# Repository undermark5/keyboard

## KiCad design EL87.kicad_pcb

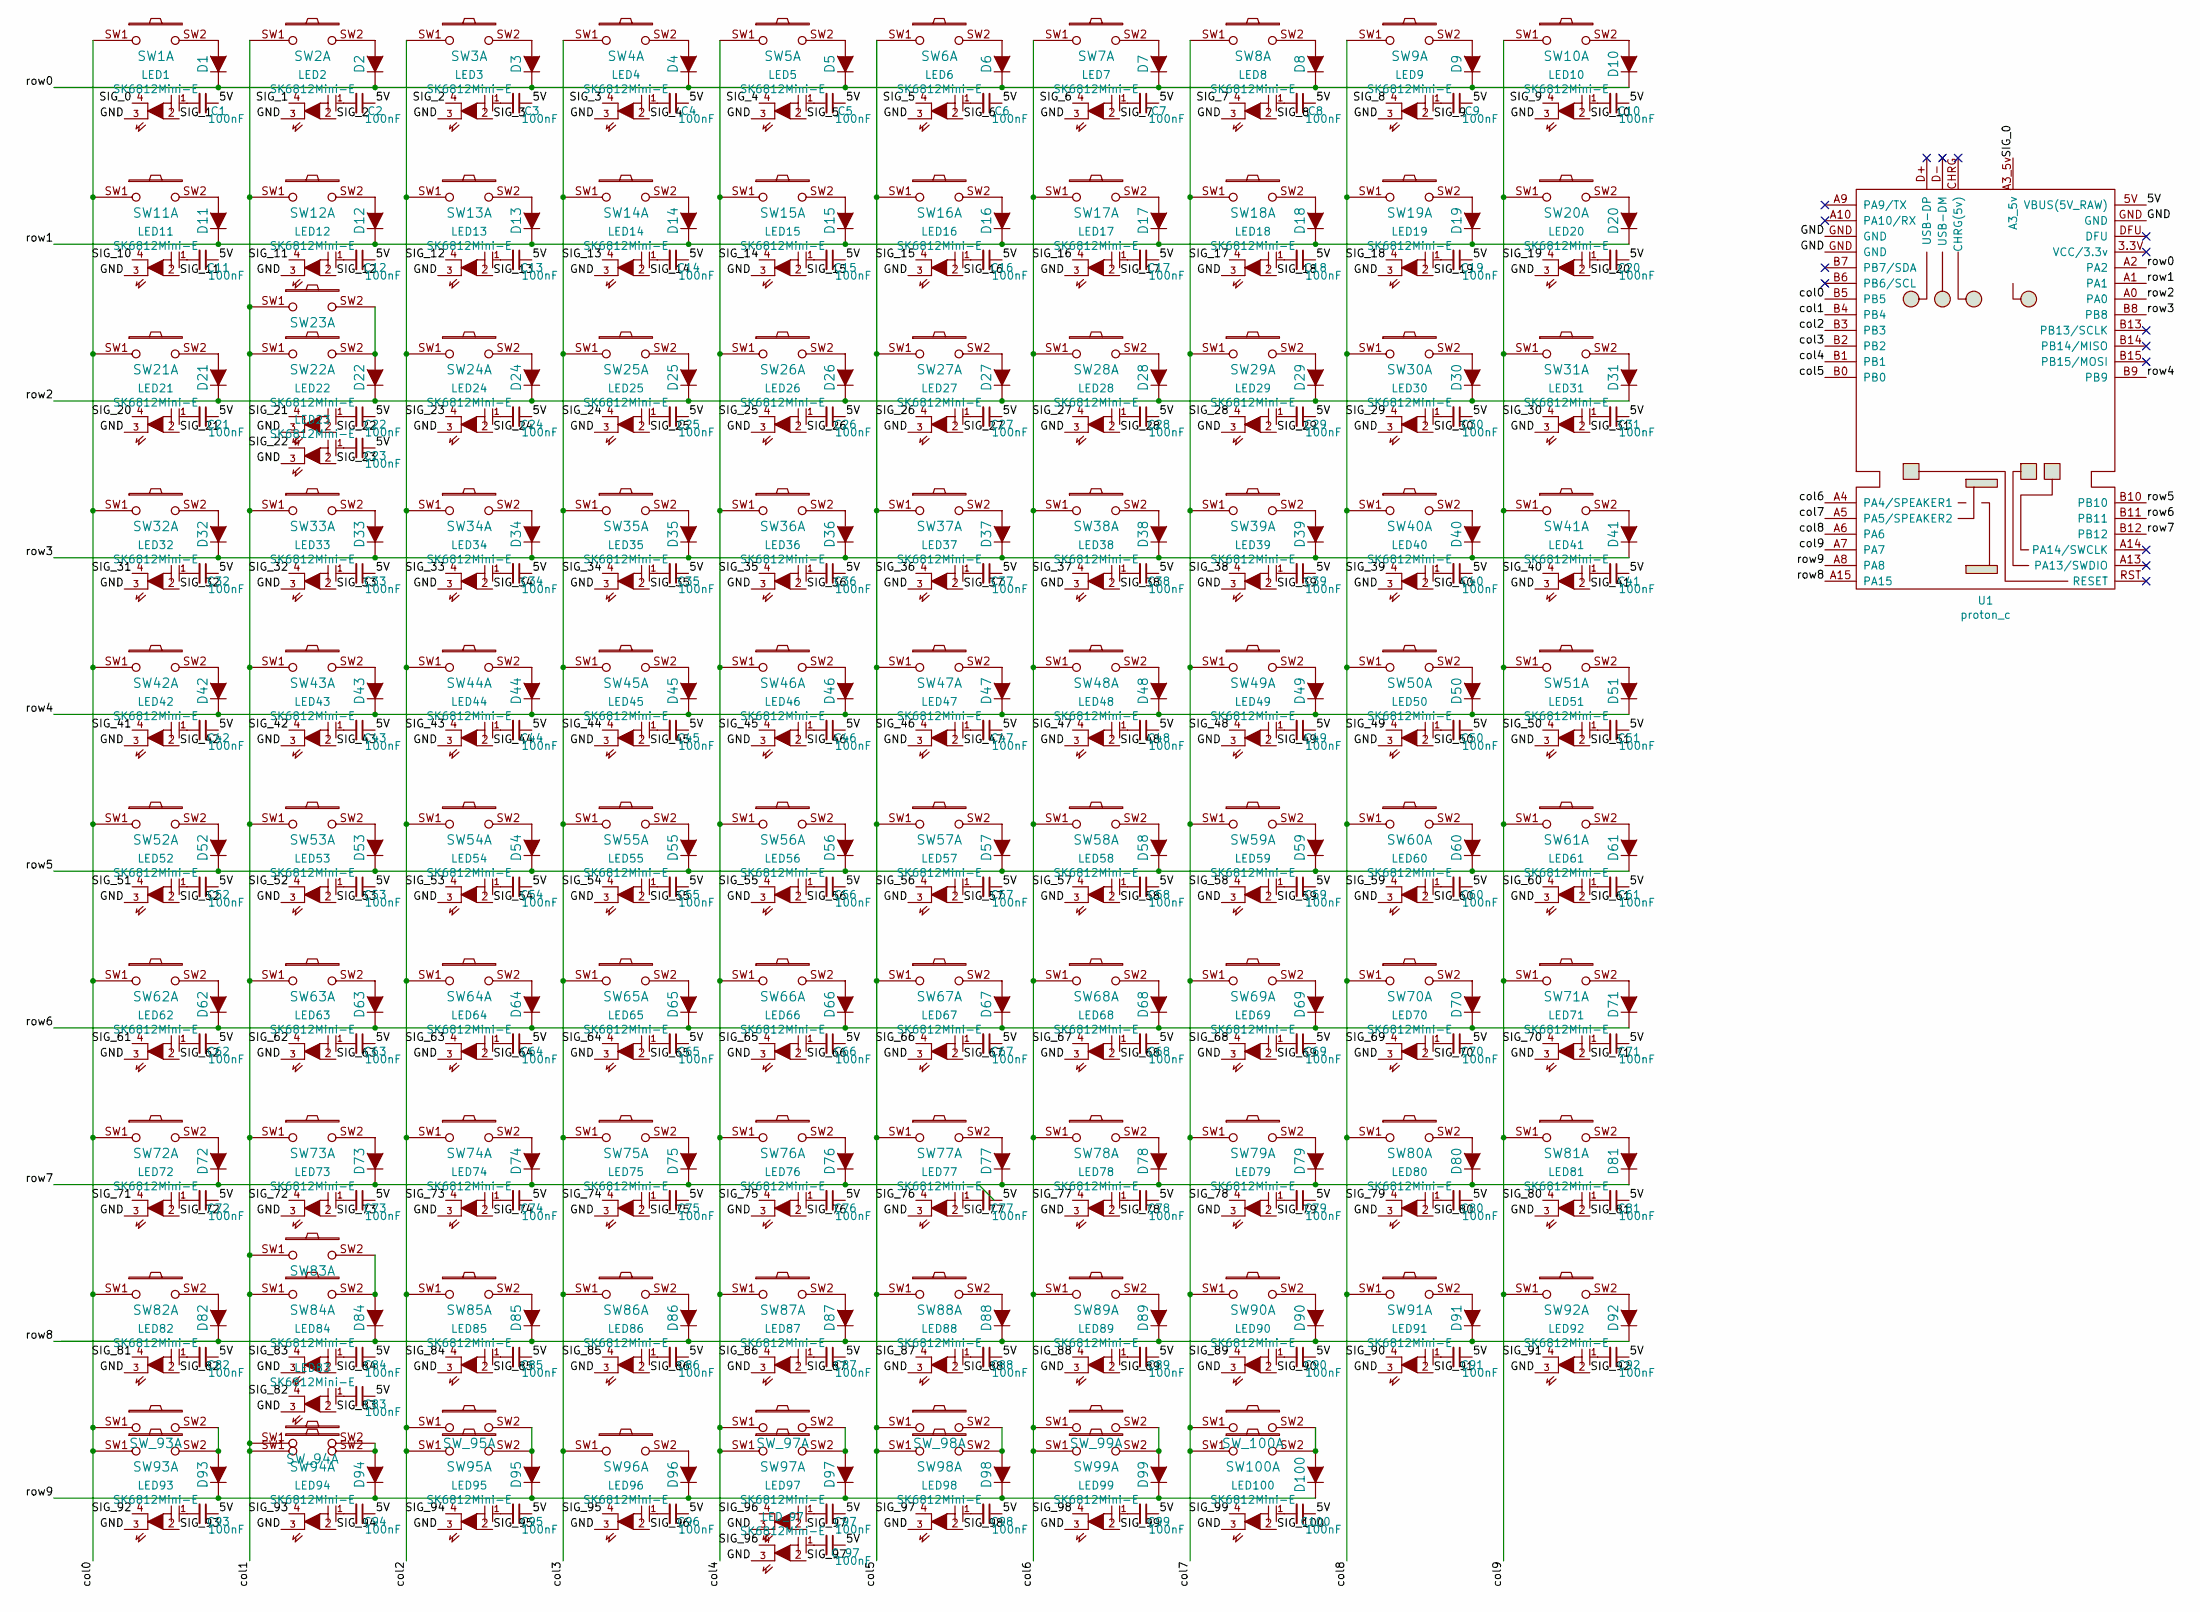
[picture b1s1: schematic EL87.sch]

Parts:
C1, C2, C3, C4, C5, C6, C7, C8, C9, C10, C11, C12, C13, C14, C15, C16, C17, C18, C19, C20, C21, C22, C23, C24, C25, C26, C27, C28, C29, C30, C31, C32, C33, C34, C35, C36, C37, C38, C39, C40, C41, C42, C43, C44, C45, C46, C47, C48, C49, C50, C51, C52, C53, C54, C55, C56, C57, C58, C59, C60, C61, C62, C63, C64, C65, C66, C67, C68, C69, C70, C71, C72, C73, C74, C75, C76, C77, C78, C79, C80, C81, C82, C83, C84, C85, C86, C87, C88, C89, C90, C91, C92, C93, C94, C95, C96, C97, C98, C99, C100: 100nF; MX-1U-0805
C_97: 100nF; MX-1U-0805
D1, D2, D3, D4, D5, D6, D7, D8, D9, D10, D11, D12, D13, D14, D15, D16, D17, D18, D19, D20, D21, D22, D24, D25, D26, D27, D28, D29, D30, D31, D32, D33, D34, D35, D36, D37, D38, D39, D40, D41, D42, D43, D44, D45, D46, D47, D48, D49, D50, D51, D52, D53, D54, D55, D56, D57, D58, D59, D60, D61, D62, D63, D64, D65, D66, D67, D68, D69, D70, D71, D72, D73, D74, D75, D76, D77, D78, D79, D80, D81, D82, D84, D85, D86, D87, D88, D89, D90, D91, D92, D93, D94, D95, D96, D97, D98, D99, D100: D; D_SOD-123_HandSoldering
LED1, LED2, LED3, LED4, LED5, LED6, LED7, LED8, LED9, LED10, LED11, LED12, LED13, LED14, LED15, LED16, LED17, LED18, LED19, LED20, LED21, LED22, LED23, LED24, LED25, LED26, LED27, LED28, LED29, LED30, LED31, LED32, LED33, LED34, LED35, LED36, LED37, LED38, LED39, LED40, LED41, LED42, LED43, LED44, LED45, LED46, LED47, LED48, LED49, LED50, LED51, LED52, LED53, LED54, LED55, LED56, LED57, LED58, LED59, LED60, LED61, LED62, LED63, LED64, LED65, LED66, LED67, LED68, LED69, LED70, LED71, LED72, LED73, LED74, LED75, LED76, LED77, LED78, LED79, LED80, LED81, LED82, LED83, LED84, LED85, LED86, LED87, LED88, LED89, LED90, LED91, LED92, LED93, LED94, LED95, LED96, LED97, LED98, LED99, LED100: SK6812Mini-E; MX-1U-KS6812Mini-E
LED_97: SK6812Mini-E; MX-1U-KS6812Mini-E
SW1: ESC; MXALPS
SW2: F1; MXALPS
SW3: F2; MXALPS
SW4: F3; MXALPS
SW5: F4; MXALPS
SW6: F5; MXALPS
SW7: F6; MXALPS_1.5U
SW8: F7; MXALPS
SW9: F8; MXALPS
SW10: F9; MXALPS
SW11: F10; MXALPS
SW12: F11; MXALPS
SW13: F12; MXALPS
SW14: PrtScrn; MXALPS
SW15: ScrlLck; MXALPS
SW16: PB; MXALPS
SW17: NumLck; MXALPS
SW18, SW26: -; MXALPS
SW19: PgUp; MXALPS
SW20: Home; MXALPS
SW21: Insert; MXALPS
SW22: BckSpc_split; MXALPS
SW23: BckSpc_2; MXALPS_2U
SW24: BckSpc_Split_2; MXALPS
SW25: =; MXALPS
SW27, SW92: 0; MXALPS
SW28: 9; MXALPS
SW29: 8; MXALPS
SW30: 7; MXALPS
SW31, SW56: 6; MXALPS
SW32: 5; MXALPS
SW33, SW58: 4; MXALPS
SW34, SW88: 3; MXALPS
SW35, SW87: 2; MXALPS
SW36, SW86: 1; MXALPS
SW37: GRAVE; MXALPS
SW38: Tab_1.5; MXALPS_1.5U
SW39: Q; MXALPS
SW40: W; MXALPS
SW41: E; MXALPS
SW42: R; MXALPS
SW43: T; MXALPS
SW44: Y; MXALPS
SW45: U; MXALPS
SW46: I; MXALPS
SW47: O; MXALPS
SW48: P; MXALPS
SW49: [; MXALPS
SW50: ]; MXALPS
SW51: \\; MXALPS
SW52: DEL; MXALPS
SW53: END; MXALPS
SW54: PGDN; MXALPS
SW55: +; MXALPS
SW57: 5; MXALPS_1.75U
SW59: Enter_2.25; MXALPS_2.25U
SW60: APOSTROPHE; MXALPS
SW61: ;; MXALPS
SW62: L; MXALPS
SW63: K; MXALPS
SW64: J; MXALPS
SW65: H; MXALPS
SW66: G; MXALPS
SW67: F; MXALPS
SW68: D; MXALPS
SW69: S; MXALPS
SW70: A; MXALPS
SW71: CAPS_1.75; MXALPS_1.75U
SW72: SHIFT_2.25; MXALPS_2.25U
SW73: Z; MXALPS
SW74: X; MXALPS
SW75: C; MXALPS
SW76: V; MXALPS
SW77: B; MXALPS
SW78: N; MXALPS
SW79: M; MXALPS
SW80: ,; MXALPS
SW81, SW90: .; MXALPS
SW82: /; MXALPS
SW83: Shift_split_1.75; MXALPS_1.75U
SW84: Shift_2.75; MXALPS_2.75U
SW85: Shift_split_fn; MXALPS
SW89: Enter; MXALPS
SW91: 00; MXALPS
SW93: Ctrl_1.25; MXALPS_1.25U
SW94: MENU_1.25; MXALPS_1.25U
SW95, SW99: GUI_1.25; MXALPS_1.25U
SW96, SW98: ALT_1.25; MXALPS_1.25U
SW97: SPACE_6.25; MXALPS_6.25U
SW100: CTRL_1.25; MXALPS_1.25U
SW_93, SW_100: CTRL_1.5; MXALPS_1.5U
SW_94, SW_99: GUI; MXALPS
SW_95, SW_98: ALT_1.5; MXALPS_1.5U
SW_97: SPACE_7; MXALPS_7U
U1: proton_c

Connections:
/5V: C1.1, C2.1, C3.1, C4.1, C5.1, C6.1, C7.1, C8.1, C9.1, C10.1, C11.1, C12.1, C13.1, C14.1, C15.1, C16.1, C17.1, C18.1, C19.1, C20.1, C21.1, C22.1, C23.1, C24.1, C25.1, C26.1, C27.1, C28.1, C29.1, C30.1, C31.1, C32.1, C33.1, C34.1, C35.1, C36.1, C37.1, C38.1, C39.1, C40.1, C41.1, C42.1, C43.1, C44.1, C45.1, C46.1, C47.1, C48.1, C49.1, C50.1, C51.1, C52.1, C53.1, C54.1, C55.1, C56.1, C57.1, C58.1, C59.1, C60.1, C61.1, C62.1, C63.1, C64.1, C65.1, C66.1, C67.1, C68.1, C69.1, C70.1, C71.1, C72.1, C73.1, C74.1, C75.1, C76.1, C77.1, C78.1, C79.1, C80.1, C81.1, C82.1, C83.1, C84.1, C85.1, C86.1, C87.1, C88.1, C89.1, C90.1, C91.1, C92.1, C93.1, C94.1, C95.1, C96.1, C97.1, C98.1, C99.1, C100.1, C_97.1, U1.5V (VBUS(5V_RAW))
/GND: LED1.3 (GND), LED2.3 (GND), LED3.3 (GND), LED4.3 (GND), LED5.3 (GND), LED6.3 (GND), LED7.3 (GND), LED8.3 (GND), LED9.3 (GND), LED10.3 (GND), LED11.3 (GND), LED12.3 (GND), LED13.3 (GND), LED14.3 (GND), LED15.3 (GND), LED16.3 (GND), LED17.3 (GND), LED18.3 (GND), LED19.3 (GND), LED20.3 (GND), LED21.3 (GND), LED22.3 (GND), LED23.3 (GND), LED24.3 (GND), LED25.3 (GND), LED26.3 (GND), LED27.3 (GND), LED28.3 (GND), LED29.3 (GND), LED30.3 (GND), LED31.3 (GND), LED32.3 (GND), LED33.3 (GND), LED34.3 (GND), LED35.3 (GND), LED36.3 (GND), LED37.3 (GND), LED38.3 (GND), LED39.3 (GND), LED40.3 (GND), LED41.3 (GND), LED42.3 (GND), LED43.3 (GND), LED44.3 (GND), LED45.3 (GND), LED46.3 (GND), LED47.3 (GND), LED48.3 (GND), LED49.3 (GND), LED50.3 (GND), LED51.3 (GND), LED52.3 (GND), LED53.3 (GND), LED54.3 (GND), LED55.3 (GND), LED56.3 (GND), LED57.3 (GND), LED58.3 (GND), LED59.3 (GND), LED60.3 (GND), LED61.3 (GND), LED62.3 (GND), LED63.3 (GND), LED64.3 (GND), LED65.3 (GND), LED66.3 (GND), LED67.3 (GND), LED68.3 (GND), LED69.3 (GND), LED70.3 (GND), LED71.3 (GND), LED72.3 (GND), LED73.3 (GND), LED74.3 (GND), LED75.3 (GND), LED76.3 (GND), LED77.3 (GND), LED78.3 (GND), LED79.3 (GND), LED80.3 (GND), LED81.3 (GND), LED82.3 (GND), LED83.3 (GND), LED84.3 (GND), LED85.3 (GND), LED86.3 (GND), LED87.3 (GND), LED88.3 (GND), LED89.3 (GND), LED90.3 (GND), LED91.3 (GND), LED92.3 (GND), LED93.3 (GND), LED94.3 (GND), LED95.3 (GND), LED96.3 (GND), LED97.3 (GND), LED98.3 (GND), LED99.3 (GND), LED100.3 (GND), LED_97.3 (GND), U1.GND
/SIG_0: LED1.4 (D_IN), U1.A3_5v
/SIG_1: LED1.2 (D_OUT), LED2.4 (D_IN)
/SIG_2: LED2.2 (D_OUT), LED3.4 (D_IN)
/SIG_3: LED3.2 (D_OUT), LED4.4 (D_IN)
/SIG_4: LED4.2 (D_OUT), LED5.4 (D_IN)
/SIG_5: LED5.2 (D_OUT), LED6.4 (D_IN)
/SIG_6: LED6.2 (D_OUT), LED7.4 (D_IN)
/SIG_7: LED7.2 (D_OUT), LED8.4 (D_IN)
/SIG_8: LED8.2 (D_OUT), LED9.4 (D_IN)
/SIG_9: LED9.2 (D_OUT), LED10.4 (D_IN)
/SIG_10: LED10.2 (D_OUT), LED11.4 (D_IN)
/SIG_11: LED11.2 (D_OUT), LED12.4 (D_IN)
/SIG_12: LED12.2 (D_OUT), LED13.4 (D_IN)
/SIG_13: LED13.2 (D_OUT), LED14.4 (D_IN)
/SIG_14: LED14.2 (D_OUT), LED15.4 (D_IN)
/SIG_15: LED15.2 (D_OUT), LED16.4 (D_IN)
/SIG_16: LED16.2 (D_OUT), LED17.4 (D_IN)
/SIG_17: LED17.2 (D_OUT), LED18.4 (D_IN)
/SIG_18: LED18.2 (D_OUT), LED19.4 (D_IN)
/SIG_19: LED19.2 (D_OUT), LED20.4 (D_IN)
/SIG_20: LED20.2 (D_OUT), LED21.4 (D_IN)
/SIG_21: LED21.2 (D_OUT), LED22.4 (D_IN); also elsewhere on the board
/SIG_22: LED22.2 (D_OUT), LED23.4 (D_IN); also elsewhere on the board
/SIG_23: LED23.2 (D_OUT), LED24.4 (D_IN); also elsewhere on the board
/SIG_24: LED24.2 (D_OUT), LED25.4 (D_IN); also elsewhere on the board
/SIG_25: LED25.2 (D_OUT), LED26.4 (D_IN)
/SIG_26: LED26.2 (D_OUT), LED27.4 (D_IN)
/SIG_27: LED27.2 (D_OUT), LED28.4 (D_IN)
/SIG_28: LED28.2 (D_OUT), LED29.4 (D_IN)
/SIG_29: LED29.2 (D_OUT), LED30.4 (D_IN)
/SIG_30: LED30.2 (D_OUT), LED31.4 (D_IN)
/SIG_31: LED31.2 (D_OUT), LED32.4 (D_IN)
/SIG_32: LED32.2 (D_OUT), LED33.4 (D_IN)
/SIG_33: LED33.2 (D_OUT), LED34.4 (D_IN)
/SIG_34: LED34.2 (D_OUT), LED35.4 (D_IN)
/SIG_35: LED35.2 (D_OUT), LED36.4 (D_IN)
/SIG_36: LED36.2 (D_OUT), LED37.4 (D_IN)
/SIG_37: LED37.2 (D_OUT), LED38.4 (D_IN)
/SIG_38: LED38.2 (D_OUT), LED39.4 (D_IN)
/SIG_39: LED39.2 (D_OUT), LED40.4 (D_IN)
/SIG_40: LED40.2 (D_OUT), LED41.4 (D_IN)
/SIG_41: LED41.2 (D_OUT), LED42.4 (D_IN)
/SIG_42: LED42.2 (D_OUT), LED43.4 (D_IN)
/SIG_43: LED43.2 (D_OUT), LED44.4 (D_IN)
/SIG_44: LED44.2 (D_OUT), LED45.4 (D_IN)
/SIG_45: LED45.2 (D_OUT), LED46.4 (D_IN)
/SIG_46: LED46.2 (D_OUT), LED47.4 (D_IN)
/SIG_47: LED47.2 (D_OUT), LED48.4 (D_IN)
/SIG_48: LED48.2 (D_OUT), LED49.4 (D_IN)
/SIG_49: LED49.2 (D_OUT), LED50.4 (D_IN)
/SIG_50: LED50.2 (D_OUT), LED51.4 (D_IN)
/SIG_51: LED51.2 (D_OUT), LED52.4 (D_IN)
/SIG_52: LED52.2 (D_OUT), LED53.4 (D_IN)
/SIG_53: LED53.2 (D_OUT), LED54.4 (D_IN)
/SIG_54: LED54.2 (D_OUT), LED55.4 (D_IN)
/SIG_55: LED55.2 (D_OUT), LED56.4 (D_IN)
/SIG_56: LED56.2 (D_OUT), LED57.4 (D_IN)
/SIG_57: LED57.2 (D_OUT), LED58.4 (D_IN)
/SIG_58: LED58.2 (D_OUT), LED59.4 (D_IN)
/SIG_59: LED59.2 (D_OUT), LED60.4 (D_IN)
/SIG_60: LED60.2 (D_OUT), LED61.4 (D_IN)
/SIG_61: LED61.2 (D_OUT), LED62.4 (D_IN)
/SIG_62: LED62.2 (D_OUT), LED63.4 (D_IN)
/SIG_63: LED63.2 (D_OUT), LED64.4 (D_IN)
/SIG_64: LED64.2 (D_OUT), LED65.4 (D_IN)
/SIG_65: LED65.2 (D_OUT), LED66.4 (D_IN)
/SIG_66: LED66.2 (D_OUT), LED67.4 (D_IN)
/SIG_67: LED67.2 (D_OUT), LED68.4 (D_IN)
/SIG_68: LED68.2 (D_OUT), LED69.4 (D_IN)
/SIG_69: LED69.2 (D_OUT), LED70.4 (D_IN)
/SIG_70: LED70.2 (D_OUT), LED71.4 (D_IN)
/SIG_71: LED71.2 (D_OUT), LED72.4 (D_IN)
/SIG_72: LED72.2 (D_OUT), LED73.4 (D_IN)
/SIG_73: LED73.2 (D_OUT), LED74.4 (D_IN)
/SIG_74: LED74.2 (D_OUT), LED75.4 (D_IN)
/SIG_75: LED75.2 (D_OUT), LED76.4 (D_IN)
/SIG_76: LED76.2 (D_OUT), LED77.4 (D_IN)
/SIG_77: LED77.2 (D_OUT), LED78.4 (D_IN)
/SIG_78: LED78.2 (D_OUT), LED79.4 (D_IN)
/SIG_79: LED79.2 (D_OUT), LED80.4 (D_IN)
/SIG_80: LED80.2 (D_OUT), LED81.4 (D_IN)
/SIG_81: LED81.2 (D_OUT), LED82.4 (D_IN)
/SIG_82: LED82.2 (D_OUT), LED83.4 (D_IN); also elsewhere on the board
/SIG_83: LED83.2 (D_OUT), LED84.4 (D_IN); also elsewhere on the board
/SIG_84: LED84.2 (D_OUT), LED85.4 (D_IN); also elsewhere on the board
/SIG_85: LED85.2 (D_OUT), LED86.4 (D_IN); also elsewhere on the board
/SIG_86: LED86.2 (D_OUT), LED87.4 (D_IN)
/SIG_87: LED87.2 (D_OUT), LED88.4 (D_IN)
/SIG_88: LED88.2 (D_OUT), LED89.4 (D_IN)
/SIG_89: LED89.2 (D_OUT), LED90.4 (D_IN)
/SIG_90: LED90.2 (D_OUT), LED91.4 (D_IN)
/SIG_91: LED91.2 (D_OUT), LED92.4 (D_IN)
/SIG_92: LED92.2 (D_OUT), LED93.4 (D_IN)
/SIG_93: LED93.2 (D_OUT), LED94.4 (D_IN)
/SIG_94: LED94.2 (D_OUT), LED95.4 (D_IN)
/SIG_95: LED95.2 (D_OUT), LED96.4 (D_IN); also elsewhere on the board
/SIG_96: LED96.2 (D_OUT), LED97.4 (D_IN), LED_97.4 (D_IN); also elsewhere on the board
/SIG_97: LED97.2 (D_OUT), LED98.4 (D_IN), LED_97.2 (D_OUT)
/SIG_98: LED98.2 (D_OUT), LED99.4 (D_IN)
/SIG_99: LED99.2 (D_OUT), LED100.4 (D_IN)
/SIG_100: LED100.2 (D_OUT)
/col0: SW1.SW1, SW11.SW1, SW21.SW1, SW32.SW1, SW42.SW1, SW52.SW1, SW62.SW1, SW72.SW1, SW82.SW1, SW93.SW1, SW_93.SW1, U1.B5
/col1: SW2.SW1, SW12.SW1, SW22.SW1, SW23.SW1, SW33.SW1, SW43.SW1, SW53.SW1, SW63.SW1, SW73.SW1, SW83.SW1, SW84.SW1, SW94.SW1, SW_94.SW1, U1.B4
/col2: SW3.SW1, SW13.SW1, SW24.SW1, SW34.SW1, SW44.SW1, SW54.SW1, SW64.SW1, SW74.SW1, SW85.SW1, SW95.SW1, SW_95.SW1, U1.B3
/col3: SW4.SW1, SW14.SW1, SW25.SW1, SW35.SW1, SW45.SW1, SW55.SW1, SW65.SW1, SW75.SW1, SW86.SW1, SW96.SW1, U1.B2
/col4: SW5.SW1, SW15.SW1, SW26.SW1, SW36.SW1, SW46.SW1, SW56.SW1, SW66.SW1, SW76.SW1, SW87.SW1, SW97.SW1, SW_97.SW1, U1.B1
/col5: SW6.SW1, SW16.SW1, SW27.SW1, SW37.SW1, SW47.SW1, SW57.SW1, SW67.SW1, SW77.SW1, SW88.SW1, SW98.SW1, SW_98.SW1, U1.B0
/col6: SW7.SW1, SW17.SW1, SW28.SW1, SW38.SW1, SW48.SW1, SW58.SW1, SW68.SW1, SW78.SW1, SW89.SW1, SW99.SW1, SW_99.SW1, U1.A4 (PA4/SPEAKER1)
/col7: SW8.SW1, SW18.SW1, SW29.SW1, SW39.SW1, SW49.SW1, SW59.SW1, SW69.SW1, SW79.SW1, SW90.SW1, SW100.SW1, SW_100.SW1, U1.A5 (PA5/SPEAKER2)
/col8: SW9.SW1, SW19.SW1, SW30.SW1, SW40.SW1, SW50.SW1, SW60.SW1, SW70.SW1, SW80.SW1, SW91.SW1, U1.A6
/col9: SW10.SW1, SW20.SW1, SW31.SW1, SW41.SW1, SW51.SW1, SW61.SW1, SW71.SW1, SW81.SW1, SW92.SW1, U1.A7
/row0: D1.1 (K), D2.1 (K), D3.1 (K), D4.1 (K), D5.1 (K), D6.1 (K), D7.1 (K), D8.1 (K), D9.1 (K), D10.1 (K), U1.A2
/row1: D11.1 (K), D12.1 (K), D13.1 (K), D14.1 (K), D15.1 (K), D16.1 (K), D17.1 (K), D18.1 (K), D19.1 (K), D20.1 (K), U1.A1
/row2: D21.1 (K), D22.1 (K), D24.1 (K), D25.1 (K), D26.1 (K), D27.1 (K), D28.1 (K), D29.1 (K), D30.1 (K), D31.1 (K), U1.A0
/row3: D32.1 (K), D33.1 (K), D34.1 (K), D35.1 (K), D36.1 (K), D37.1 (K), D38.1 (K), D39.1 (K), D40.1 (K), D41.1 (K), U1.B8
/row4: D42.1 (K), D43.1 (K), D44.1 (K), D45.1 (K), D46.1 (K), D47.1 (K), D48.1 (K), D49.1 (K), D50.1 (K), D51.1 (K), U1.B9
/row5: D52.1 (K), D53.1 (K), D54.1 (K), D55.1 (K), D56.1 (K), D57.1 (K), D58.1 (K), D59.1 (K), D60.1 (K), D61.1 (K), U1.B10
/row6: D62.1 (K), D63.1 (K), D64.1 (K), D65.1 (K), D66.1 (K), D67.1 (K), D68.1 (K), D69.1 (K), D70.1 (K), D71.1 (K), U1.B11
/row7: D72.1 (K), D73.1 (K), D74.1 (K), D75.1 (K), D76.1 (K), D77.1 (K), D78.1 (K), D79.1 (K), D80.1 (K), D81.1 (K), U1.B12
/row8: D82.1 (K), D84.1 (K), D85.1 (K), D86.1 (K), D87.1 (K), D88.1 (K), D89.1 (K), D90.1 (K), D91.1 (K), D92.1 (K), U1.A15
/row9: D93.1 (K), D94.1 (K), D95.1 (K), D96.1 (K), D97.1 (K), D98.1 (K), D99.1 (K), D100.1 (K), U1.A8
unnamed: C1.2, LED1.1 (VDD)
unnamed: C2.2, LED2.1 (VDD)
unnamed: C3.2, LED3.1 (VDD)
unnamed: C4.2, LED4.1 (VDD)
unnamed: C5.2, LED5.1 (VDD)
unnamed: C6.2, LED6.1 (VDD)
unnamed: C7.2, LED7.1 (VDD)
unnamed: C8.2, LED8.1 (VDD)
unnamed: C9.2, LED9.1 (VDD)
unnamed: C10.2, LED10.1 (VDD)
unnamed: C11.2, LED11.1 (VDD)
unnamed: C12.2, LED12.1 (VDD)
unnamed: C13.2, LED13.1 (VDD)
unnamed: C14.2, LED14.1 (VDD)
unnamed: C15.2, LED15.1 (VDD)
unnamed: C16.2, LED16.1 (VDD)
unnamed: C17.2, LED17.1 (VDD)
unnamed: C18.2, LED18.1 (VDD)
unnamed: C19.2, LED19.1 (VDD)
unnamed: C20.2, LED20.1 (VDD)
unnamed: C21.2, LED21.1 (VDD)
unnamed: C22.2, LED22.1 (VDD)
unnamed: C23.2, LED23.1 (VDD)
unnamed: C24.2, LED24.1 (VDD)
unnamed: C25.2, LED25.1 (VDD)
unnamed: C26.2, LED26.1 (VDD)
unnamed: C27.2, LED27.1 (VDD)
unnamed: C28.2, LED28.1 (VDD)
unnamed: C29.2, LED29.1 (VDD)
unnamed: C30.2, LED30.1 (VDD)
unnamed: C31.2, LED31.1 (VDD)
unnamed: C32.2, LED32.1 (VDD)
unnamed: C33.2, LED33.1 (VDD)
unnamed: C34.2, LED34.1 (VDD)
unnamed: C35.2, LED35.1 (VDD)
unnamed: C36.2, LED36.1 (VDD)
unnamed: C37.2, LED37.1 (VDD)
unnamed: C38.2, LED38.1 (VDD)
unnamed: C39.2, LED39.1 (VDD)
unnamed: C40.2, LED40.1 (VDD)
unnamed: C41.2, LED41.1 (VDD)
unnamed: C42.2, LED42.1 (VDD)
unnamed: C43.2, LED43.1 (VDD)
unnamed: C44.2, LED44.1 (VDD)
unnamed: C45.2, LED45.1 (VDD)
unnamed: C46.2, LED46.1 (VDD)
unnamed: C47.2, LED47.1 (VDD)
unnamed: C48.2, LED48.1 (VDD)
unnamed: C49.2, LED49.1 (VDD)
unnamed: C50.2, LED50.1 (VDD)
unnamed: C51.2, LED51.1 (VDD)
unnamed: C52.2, LED52.1 (VDD)
unnamed: C53.2, LED53.1 (VDD)
unnamed: C54.2, LED54.1 (VDD)
unnamed: C55.2, LED55.1 (VDD)
unnamed: C56.2, LED56.1 (VDD)
unnamed: C57.2, LED57.1 (VDD)
unnamed: C58.2, LED58.1 (VDD)
unnamed: C59.2, LED59.1 (VDD)
unnamed: C60.2, LED60.1 (VDD)
unnamed: C61.2, LED61.1 (VDD)
unnamed: C62.2, LED62.1 (VDD)
unnamed: C63.2, LED63.1 (VDD)
unnamed: C64.2, LED64.1 (VDD)
unnamed: C65.2, LED65.1 (VDD)
unnamed: C66.2, LED66.1 (VDD)
unnamed: C67.2, LED67.1 (VDD)
unnamed: C68.2, LED68.1 (VDD)
unnamed: C69.2, LED69.1 (VDD)
unnamed: C70.2, LED70.1 (VDD)
unnamed: C71.2, LED71.1 (VDD)
unnamed: C72.2, LED72.1 (VDD)
unnamed: C73.2, LED73.1 (VDD)
unnamed: C74.2, LED74.1 (VDD)
unnamed: C75.2, LED75.1 (VDD)
unnamed: C76.2, LED76.1 (VDD)
unnamed: C77.2, LED77.1 (VDD)
unnamed: C78.2, LED78.1 (VDD)
unnamed: C79.2, LED79.1 (VDD)
unnamed: C80.2, LED80.1 (VDD)
unnamed: C81.2, LED81.1 (VDD)
unnamed: C82.2, LED82.1 (VDD)
unnamed: C83.2, LED83.1 (VDD)
unnamed: C84.2, LED84.1 (VDD)
unnamed: C85.2, LED85.1 (VDD)
unnamed: C86.2, LED86.1 (VDD)
unnamed: C87.2, LED87.1 (VDD)
unnamed: C88.2, LED88.1 (VDD)
unnamed: C89.2, LED89.1 (VDD)
unnamed: C90.2, LED90.1 (VDD)
unnamed: C91.2, LED91.1 (VDD)
unnamed: C92.2, LED92.1 (VDD)
unnamed: C93.2, LED93.1 (VDD)
unnamed: C94.2, LED94.1 (VDD)
unnamed: C95.2, LED95.1 (VDD)
unnamed: C96.2, LED96.1 (VDD)
unnamed: C97.2, LED97.1 (VDD)
unnamed: C98.2, LED98.1 (VDD)
unnamed: C99.2, LED99.1 (VDD)
unnamed: C100.2, LED100.1 (VDD)
unnamed: C_97.2, LED_97.1 (VDD)
unnamed: D1.2 (A), SW1.SW2
unnamed: D2.2 (A), SW2.SW2
unnamed: D3.2 (A), SW3.SW2
unnamed: D4.2 (A), SW4.SW2
unnamed: D5.2 (A), SW5.SW2
unnamed: D6.2 (A), SW6.SW2
unnamed: D7.2 (A), SW7.SW2
unnamed: D8.2 (A), SW8.SW2
unnamed: D9.2 (A), SW9.SW2
unnamed: D10.2 (A), SW10.SW2
unnamed: D11.2 (A), SW11.SW2
unnamed: D12.2 (A), SW12.SW2
unnamed: D13.2 (A), SW13.SW2
unnamed: D14.2 (A), SW14.SW2
unnamed: D15.2 (A), SW15.SW2
unnamed: D16.2 (A), SW16.SW2
unnamed: D17.2 (A), SW17.SW2
unnamed: D18.2 (A), SW18.SW2
unnamed: D19.2 (A), SW19.SW2
unnamed: D20.2 (A), SW20.SW2
unnamed: D21.2 (A), SW21.SW2
unnamed: D22.2 (A), SW22.SW2, SW23.SW2
unnamed: D24.2 (A), SW24.SW2
unnamed: D25.2 (A), SW25.SW2
unnamed: D26.2 (A), SW26.SW2
unnamed: D27.2 (A), SW27.SW2
unnamed: D28.2 (A), SW28.SW2
unnamed: D29.2 (A), SW29.SW2
unnamed: D30.2 (A), SW30.SW2
unnamed: D31.2 (A), SW31.SW2
unnamed: D32.2 (A), SW32.SW2
unnamed: D33.2 (A), SW33.SW2
unnamed: D34.2 (A), SW34.SW2
unnamed: D35.2 (A), SW35.SW2
unnamed: D36.2 (A), SW36.SW2
unnamed: D37.2 (A), SW37.SW2
unnamed: D38.2 (A), SW38.SW2
unnamed: D39.2 (A), SW39.SW2
unnamed: D40.2 (A), SW40.SW2
unnamed: D41.2 (A), SW41.SW2
unnamed: D42.2 (A), SW42.SW2
unnamed: D43.2 (A), SW43.SW2
unnamed: D44.2 (A), SW44.SW2
unnamed: D45.2 (A), SW45.SW2
unnamed: D46.2 (A), SW46.SW2
unnamed: D47.2 (A), SW47.SW2
unnamed: D48.2 (A), SW48.SW2
unnamed: D49.2 (A), SW49.SW2
unnamed: D50.2 (A), SW50.SW2
unnamed: D51.2 (A), SW51.SW2
unnamed: D52.2 (A), SW52.SW2
unnamed: D53.2 (A), SW53.SW2
unnamed: D54.2 (A), SW54.SW2
unnamed: D55.2 (A), SW55.SW2
unnamed: D56.2 (A), SW56.SW2
unnamed: D57.2 (A), SW57.SW2
unnamed: D58.2 (A), SW58.SW2
unnamed: D59.2 (A), SW59.SW2
unnamed: D60.2 (A), SW60.SW2
unnamed: D61.2 (A), SW61.SW2
unnamed: D62.2 (A), SW62.SW2
unnamed: D63.2 (A), SW63.SW2
unnamed: D64.2 (A), SW64.SW2
unnamed: D65.2 (A), SW65.SW2
unnamed: D66.2 (A), SW66.SW2
unnamed: D67.2 (A), SW67.SW2
unnamed: D68.2 (A), SW68.SW2
unnamed: D69.2 (A), SW69.SW2
unnamed: D70.2 (A), SW70.SW2
unnamed: D71.2 (A), SW71.SW2
unnamed: D72.2 (A), SW72.SW2
unnamed: D73.2 (A), SW73.SW2
unnamed: D74.2 (A), SW74.SW2
unnamed: D75.2 (A), SW75.SW2
unnamed: D76.2 (A), SW76.SW2
unnamed: D77.2 (A), SW77.SW2
unnamed: D78.2 (A), SW78.SW2
unnamed: D79.2 (A), SW79.SW2
unnamed: D80.2 (A), SW80.SW2
unnamed: D81.2 (A), SW81.SW2
unnamed: D82.2 (A), SW82.SW2
unnamed: D84.2 (A), SW83.SW2, SW84.SW2
unnamed: D85.2 (A), SW85.SW2
unnamed: D86.2 (A), SW86.SW2
unnamed: D87.2 (A), SW87.SW2
unnamed: D88.2 (A), SW88.SW2
unnamed: D89.2 (A), SW89.SW2
unnamed: D90.2 (A), SW90.SW2
unnamed: D91.2 (A), SW91.SW2
unnamed: D92.2 (A), SW92.SW2
unnamed: D93.2 (A), SW93.SW2, SW_93.SW2
unnamed: D94.2 (A), SW94.SW2, SW_94.SW2
unnamed: D95.2 (A), SW95.SW2, SW_95.SW2
unnamed: D96.2 (A), SW96.SW2
unnamed: D97.2 (A), SW97.SW2, SW_97.SW2
unnamed: D98.2 (A), SW98.SW2, SW_98.SW2
unnamed: D99.2 (A), SW99.SW2, SW_99.SW2
unnamed: D100.2 (A), SW100.SW2, SW_100.SW2

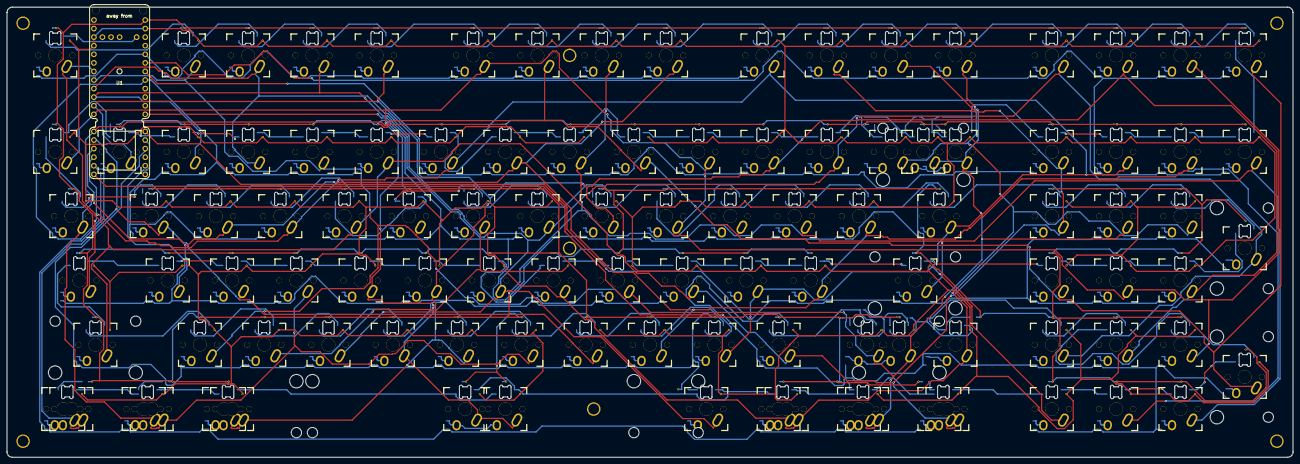
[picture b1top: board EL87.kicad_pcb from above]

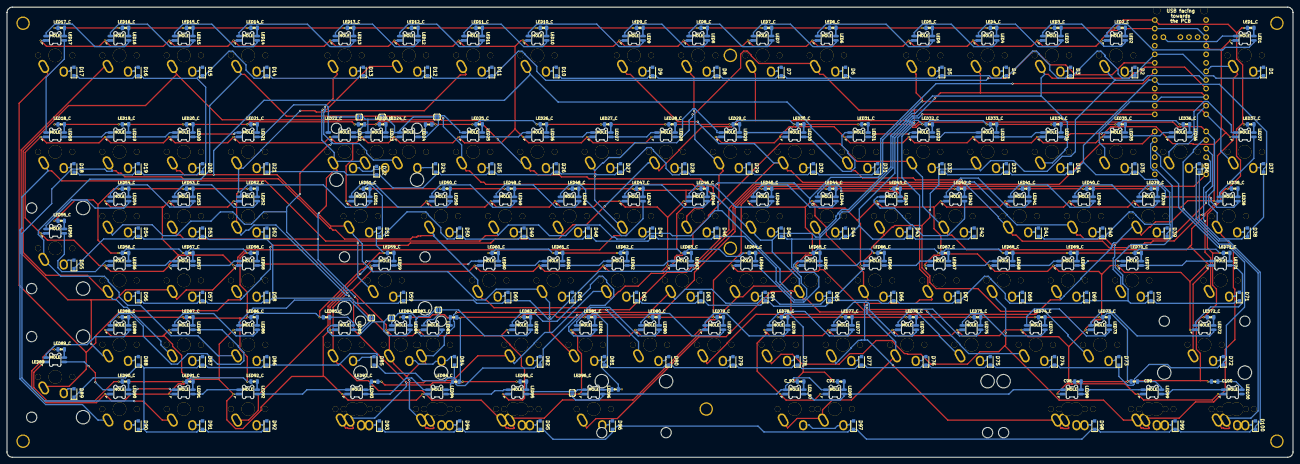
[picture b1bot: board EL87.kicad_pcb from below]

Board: 2 copper layers, 381.0 x 133.4 mm, 430 parts (206 on the bottom side), 321 nets.

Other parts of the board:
6.25U_stab: 6.25U; 6.25UReversedStabs
7U_STAB: 7U
ENTER_STAB1: 2.25U
HOLE_M3_1: 1; HOLE_M3
HOLE_M3_2: 2; HOLE_M3
HOLE_M3_3: 3; HOLE_M3
HOLE_M3_4: 4; HOLE_M3
HOLE_M3_5: 5; HOLE_M3
HOLE_M3_6, HOLE_M3_6#2: 6; HOLE_M3
JP1, JP2, JP3, JP4, JP5, JP6, JP7: SOLDER_JUMPER_2
NUMPAD_STAB1, NUMPAD_STAB2: 2.25U
STAB99: 2.75U
STAB_2: 2U_stab
stab1: 2.25U

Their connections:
/SIG_21: JP5.2; also elsewhere on the board
/SIG_22: JP5.1, JP6.2; also elsewhere on the board
/SIG_23: JP6.1, JP7.2; also elsewhere on the board
/SIG_24: JP7.1; also elsewhere on the board
/SIG_82: JP2.1; also elsewhere on the board
/SIG_83: JP2.2, JP3.1; also elsewhere on the board
/SIG_84: JP3.2, JP4.1; also elsewhere on the board
/SIG_85: JP4.2; also elsewhere on the board
/SIG_95: JP1.2; also elsewhere on the board
/SIG_96: JP1.1; also elsewhere on the board

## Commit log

2020-09-02 initial WIP
2020-09-04 gridified schematic leds might need to be moved on pcb to be more linear
2020-09-04 organized schematic pcb laid out added pdfs of schematic and pcb
2020-09-05 updated bottom row to be standard arranged LEDs to snake from top left to bottom left updated values to match key size cleaned up silk screens
2020-09-06 rerouted traces
2020-09-10 changed matrix to have columns follow physical rows to make layout easier to understand
2020-09-10 Updated the PDFs Rerouted some tracks
2020-09-20 Added alternative layouts
2020-10-11 added mounting holes. changed diodes to proper footprint.
2020-11-20 verified LED layout
